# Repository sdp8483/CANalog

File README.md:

# CANalog

CAN to analog converter.

## TODO
### PCB
- [x] Add resistor to stm32 reset line so that stm32 programmer can reset uC when esp8266 is pulling pin high
- [x] Increase clearance between terminals and mounting holes by about 1mm
- [x] Increase spacing between aout terminal and CAN terminal, possibly center CAN terminal.
- [ ] add 16bit DAC
### WiFi Interface Firmware
- [ ] fix webpage layout for mobile devices
- [ ] aout control for analog calibration
- [ ] setup over the air update for esp8266 firmware
### CAN Interface Firmware
- [ ] LED persistance for CAN activity
- [ ] setup bootloader over spi for wifi update of firmware
- [ ] setup CAN filtering
- [ ] test std ID CAN messages
- [ ] test timing
- [ ] write code to detect versioning pins

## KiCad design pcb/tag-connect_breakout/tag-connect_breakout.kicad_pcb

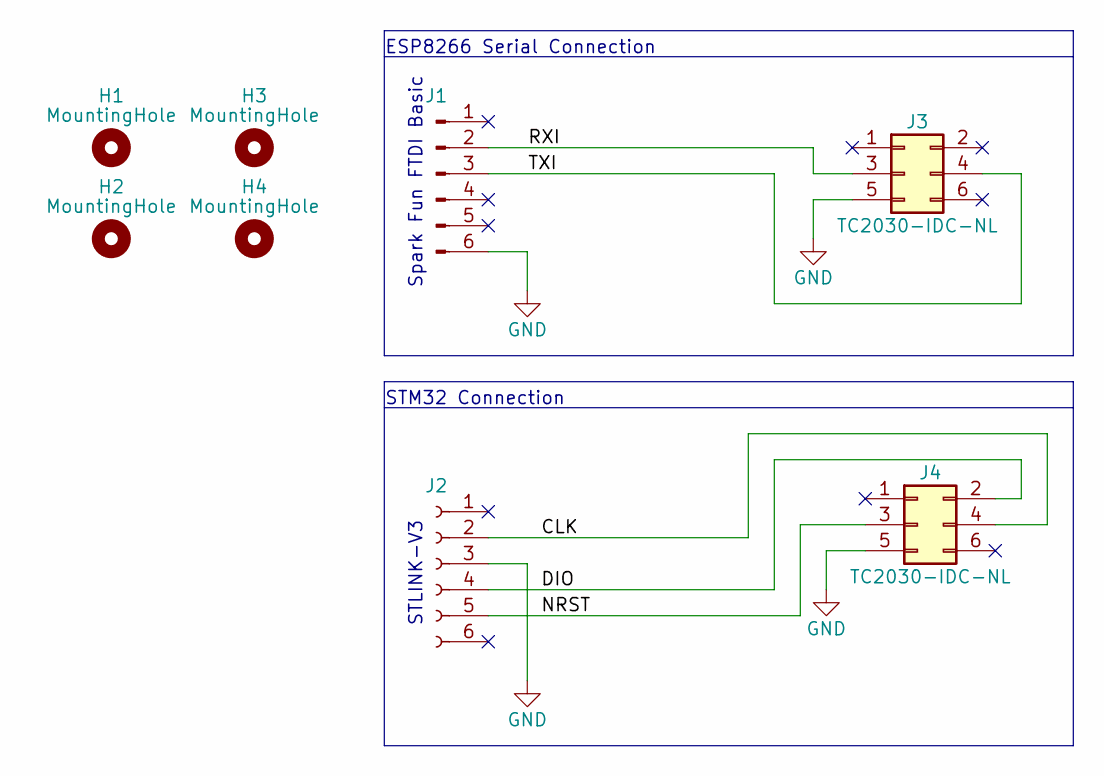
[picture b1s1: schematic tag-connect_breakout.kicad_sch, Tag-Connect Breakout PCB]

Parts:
H1, H2, H3, H4: MountingHole; MountingHole_3.2mm_M3
J1: Conn_01x06_Male; PinHeader_1x06_P2.54mm_Vertical
J2: Conn_01x06_Female; PinSocket_1x06_P2.54mm_Vertical
J3, J4: TC2030-IDC-NL; PinHeader_2x03_P2.54mm_Vertical

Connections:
/CLK: J2.2, J4.4
/DIO: J2.4, J4.2
/NRST: J2.5, J4.3
/RXI: J1.2, J3.3
/TXI: J1.3, J3.4
GND: J1.6, J2.3, J3.5, J4.5

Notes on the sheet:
Spark Fun FTDI Basic
STM32 Connection
ESP8266 Serial Connection
STLINK-V3

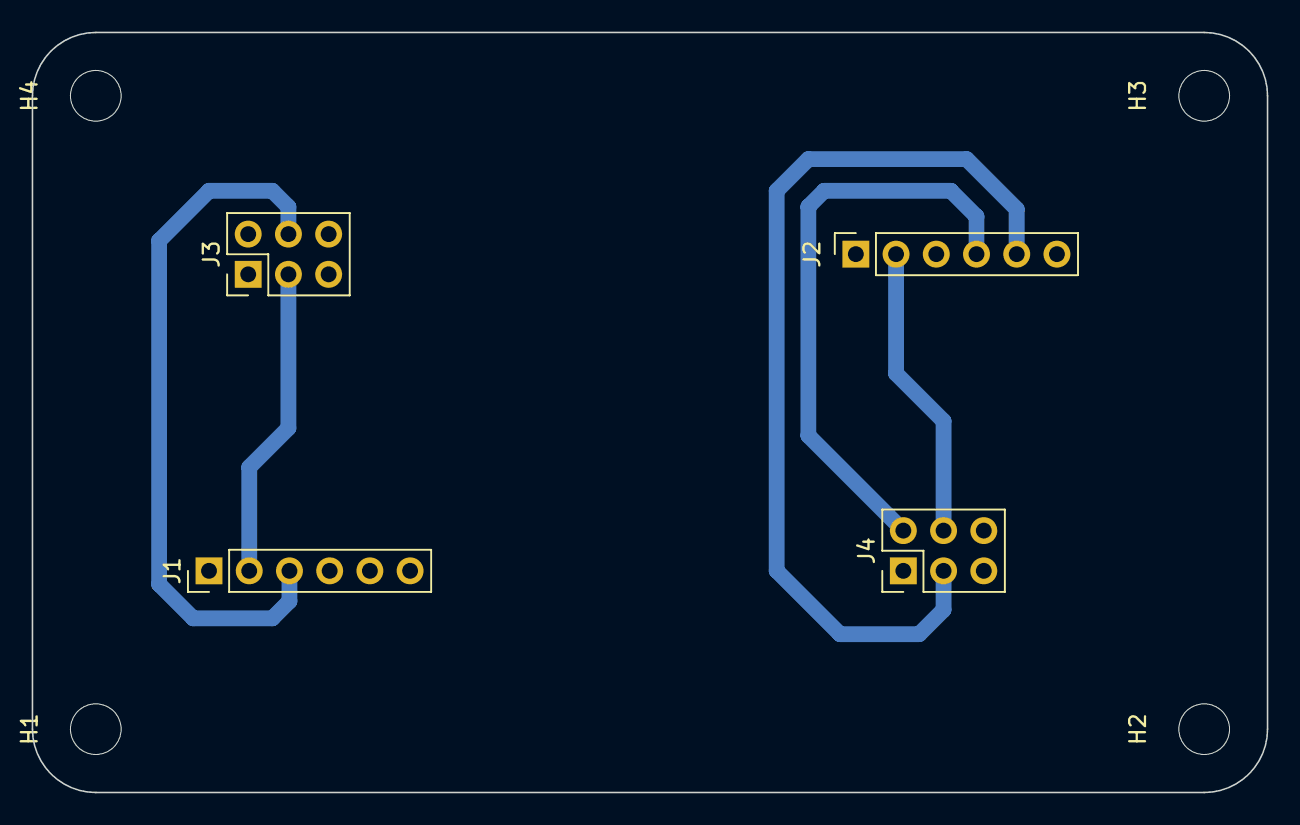
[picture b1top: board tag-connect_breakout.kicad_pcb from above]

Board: 2 copper layers, 78.0 x 48.0 mm, 8 parts (0 on the bottom side), 6 nets.

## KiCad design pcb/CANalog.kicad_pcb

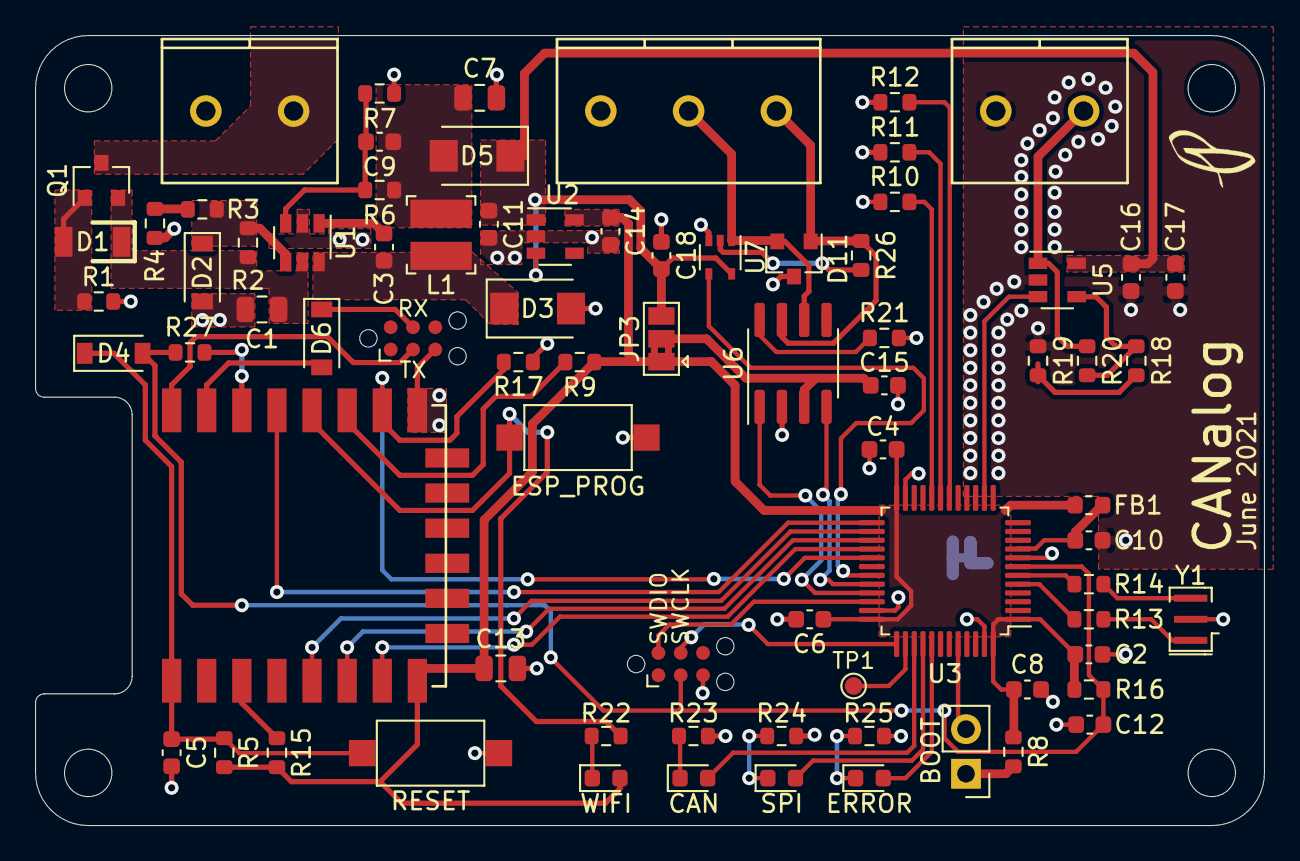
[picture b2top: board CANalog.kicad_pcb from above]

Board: 2 copper layers, 70.0 x 45.0 mm, 82 parts (1 on the bottom side), 59 nets.

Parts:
C1: 4.7uF; C_0805_2012Metric
C2, C11, C14, C17: 1uF; C_0603_1608Metric
C3, C4, C5, C6, C8, C10, C12, C15, C16, C18: 100nF; C_0603_1608Metric
C7, C13: 10uF; C_0805_2012Metric
C9: 33pF; C_0603_1608Metric
D1: BZV55-C15; Nexperia_BZV55_SOD80C
D2: 4.7V; D_SOD-123
D3, D5: SS14F; SMAF
D4, D6: 1N4148W; D_SOD-123
D7: GRN; LED_0603_1608Metric
D8: ORG; LED_0603_1608Metric
D9: RED; LED_0603_1608Metric
D10: BLU; LED_0603_1608Metric
D11: PESD1CAN; SOT-23
FB1: FBS; L_0603_1608Metric
H1, H2, H3, H4: MountingHole; MountingHole_2.7mm_M2.5
J1: PWR; WJ127-5.0-2P
J4: STM_PROG; Tag-Connect_TC2030-IDC-NL_2x03_P1.27mm_Vertical
J5: ESP_PROG; Tag-Connect_TC2030-IDC-NL_2x03_P1.27mm_Vertical
J6: AOUT; WJ127-5.0-2P
J7: CAN; WJ127-5.0-3P
JP2: BOOT0; PinHeader_1x02_P2.54mm_Vertical
JP3: PSELECT; SolderJumper-3_P1.3mm_Bridged2Bar12_Pad1.0x1.5mm
L1: 2.2uH; L_3.5mmx3.0mm_SMD
NT1: Net-Tie_2; NetTie-2_SMD_Pad0.5mm
Q1: DMP3099L-7; SOT-23
R1, R5, R9, R15, R16, R17: 10k; R_0603_1608Metric
R2, R18: 120k; R_0603_1608Metric
R3: 20k; R_0603_1608Metric
R4, R19: 12k; R_0603_1608Metric
R6: 124k; R_0603_1608Metric
R7: 20.5k; R_0603_1608Metric
R8, R10, R11, R12, R22, R23, R24, R25, R27: 1k; R_0603_1608Metric
R13, R14: R; R_0603_1608Metric
R20: 68k; R_0603_1608Metric
R21: 0; R_0603_1608Metric
R26: 120; R_0603_1608Metric
SW1: RESET; SW_SPST_CK_RS282G05A3
SW2: ESP_PROG; SW_SPST_CK_RS282G05A3
TP1: PA15; TestPoint_Pad_D1.0mm
U1: BL9342; SOT-23-6
U2: MIC5504-3.3YM5; SOT-23-5
U3: STM32F302C8T6; LQFP-48_7x7mm_P0.5mm
U4: ESP-12F; ESP-12E_SMD
U5: OPA330xxDBV; SOT-23-5
U6: SN65HVD230; SOIC-8_3.9x4.9mm_P1.27mm
U7: 74AHC1G66; SOT-353_SC-70-5
Y1: 16MHz; Resonator_SMD_muRata_CSTxExxV-3Pin_3.0x1.1mm

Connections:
+3V3: C2.1, C4.1, C6.1, C8.1, C13.1, C14.1, D10.2, FB1.1, JP3.1, R5.1, R8.1, R9.1, R15.1, R16.1, U2.5, U3.1, U3.24, U3.36, U3.48, U4.8
+5V: C11.1, C16.1, C17.1, C18.2, D5.1, JP3.3, U2.1, U2.3, U5.5, U7.5
/5V5: C7.1, C9.1, D5.2, L1.2, R6.1
/BOOT0: JP2.2, U3.44
/CANH: D11.1, J7.1, R26.1, U6.7
/CANL: D11.2, J7.2, U6.6, U7.1
/GPIO15: R27.2, U4.14
/OA_PWR: C15.2, JP3.2, U6.3
/RXD: D6.2, U4.15
/SWCLK: J4.4, U3.37
/SWDIO: J4.2, U3.34
/TXD: J5.3, U4.16
/Vin: C1.1, D1.1, Q1.2, R2.2, U1.5
/XIN: R13.1, U3.5
/XOUT: R14.1, U3.6
CAN_LED: D7.2, U3.39
CAN_RX: U3.32, U6.4
CAN_TERM: U3.31, U7.4
CAN_TX: U3.33, U6.1
CH_PD: R15.2, U4.3
DAC: U3.14, U5.3
ERROR_LED: D9.2, U3.41
ESP_RESET: C5.1, D4.1, R5.2, SW1.2, U4.1
GND: C1.2, C2.2, C4.2, C5.2, C6.2, C7.2, C8.2, C11.2, C12.1, C13.2, C14.2, C15.1, C18.1, D2.2, D3.2, D11.3, J1.2, J4.5, J5.5, J7.3, NT1.1, R1.2, R4.1, R7.1, R10.1, R11.1, R12.1, R17.2, R21.2, R23.1, R24.1, R25.1, SW1.1, SW2.1, U1.2, U2.2, U3.23, U3.35, U3.47, U4.9, U6.2, U7.3, Y1.2
GNDA: C10.2, C16.2, C17.2, J6.2, NT1.2, R19.2, U3.8, U5.2
GPIO0: R22.2, SW2.2, U4.12
GPIO2: R9.2, U4.11
MISO: U3.27, U4.6
MOSI: U3.28, U4.7
unnamed: C3.1, D3.1, L1.1, U1.6
unnamed: C3.2, U1.1
unnamed: C9.2, R6.2, R7.2, U1.3
unnamed: D1.2, Q1.1, R1.1
unnamed: D2.1, R2.1, R3.2, U1.4
unnamed: D6.1, J5.4
unnamed: D7.1, R23.2
unnamed: D8.1, R24.2
unnamed: D9.1, R25.2
unnamed: D10.1, R22.1
unnamed: J1.1, Q1.3
unnamed: J6.1, R20.1, U5.1
unnamed: JP2.1, R8.2
unnamed: R3.1, R4.2
unnamed: R13.2, Y1.1
unnamed: R14.2, Y1.3
unnamed: R18.1, R20.2, U5.4
unnamed: R18.2, R19.1
unnamed: R21.1, U6.8
unnamed: R26.2, U7.2
unnamed: TP1.1, U3.38
SCLK: U3.26, U4.5
SPI_LED: D8.2, U3.40
STM_CS: R17.1, U3.29, U4.10
STM_RDY: U3.25, U4.13
STM_RESET: C12.2, D4.2, J4.3, R16.2, R27.1, U3.7
VDDA: C10.1, FB1.2, U3.9
V_B0: R12.2, U3.18
V_B1: R11.2, U3.19
V_B2: R10.2, U3.20

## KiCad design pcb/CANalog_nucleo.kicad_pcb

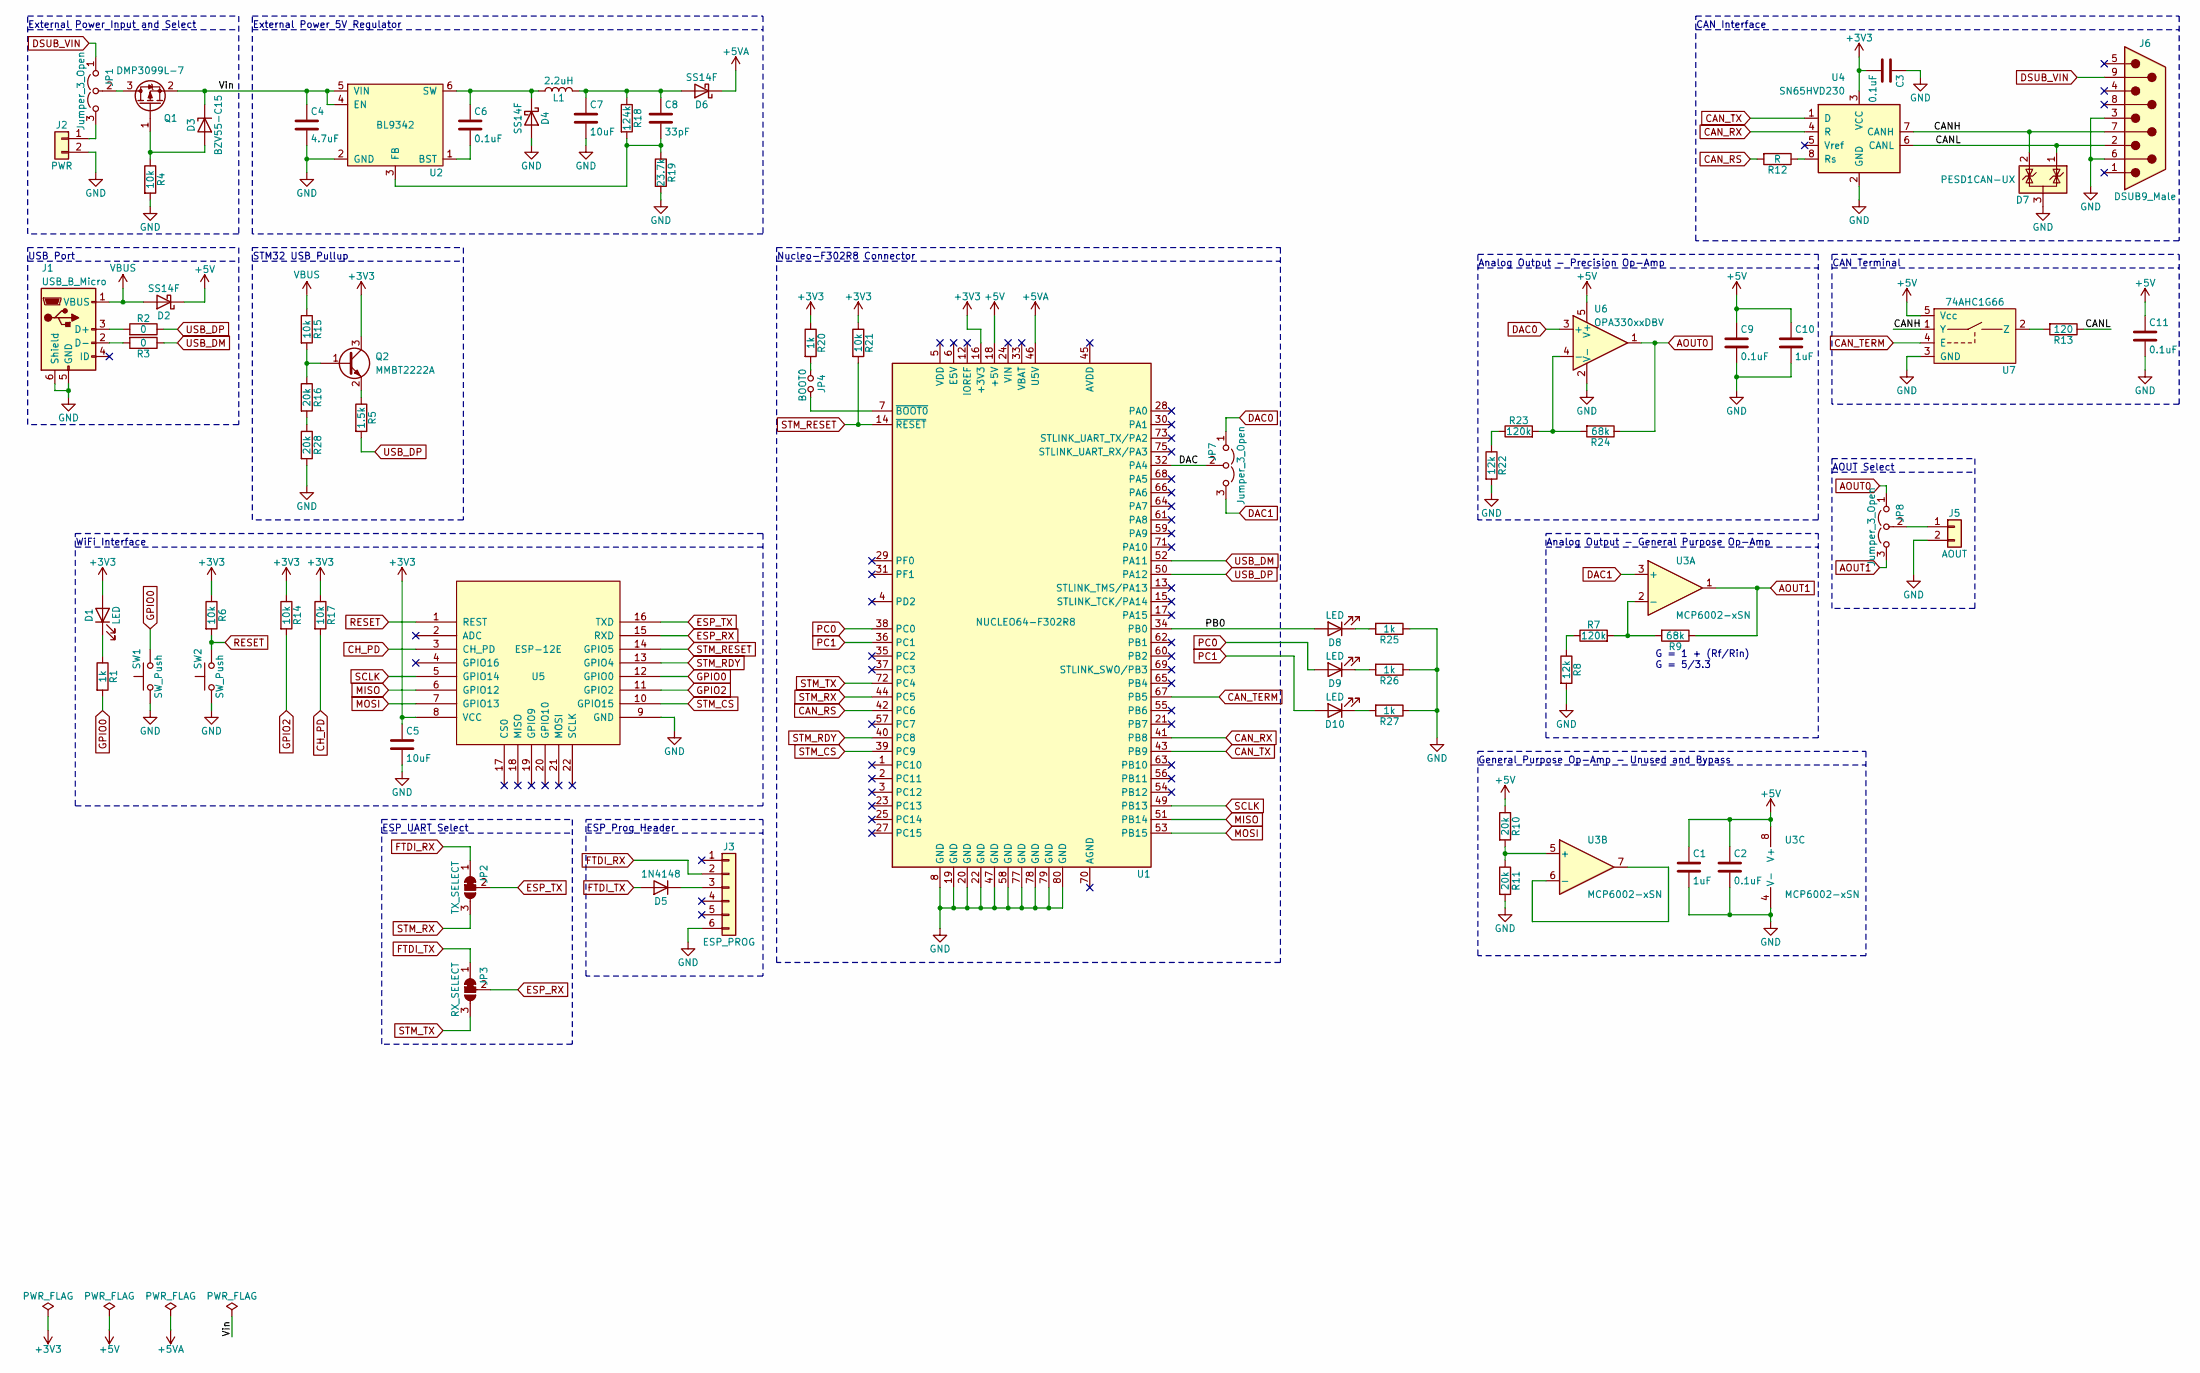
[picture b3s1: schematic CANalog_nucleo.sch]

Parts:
C1, C10: 1uF; C_0805_2012Metric
C2, C3, C6, C9, C11: 0.1uF; C_0805_2012Metric
C4: 4.7uF; C_0805_2012Metric
C5, C7: 10uF; C_0805_2012Metric
C8: 33pF; C_0603_1608Metric
D1, D8, D9, D10: LED; LED_0603_1608Metric
D2, D4, D6: SS14F; SMAF
D3: BZV55-C15; Nexperia_BZV55_SOD80C
D5: 1N4148; D_DO-35_SOD27_P7.62mm_Horizontal
D7: PESD1CAN-UX; SOT-323_SC-70
J1: USB_B_Micro; USB_Micro-B_Amphenol_10103594-0001LF_Horizontal
J2: PWR; WJ127-5.0-2P
J3: ESP_PROG; PinHeader_1x06_P2.54mm_Vertical
J5: AOUT; WJ127-5.0-2P
J6: DSUB9_Male; DSUB-9_Male_Horizontal_P2.77x2.84mm_EdgePinOffset7.70mm_Hou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
JP1, JP7, JP8: Jumper_3_Open; PinHeader_1x03_P2.54mm_Vertical
JP2: TX_SELECT; SolderJumper-3_P1.3mm_Bridged12_RoundedPad1.0x1.5mm
JP3: RX_SELECT; SolderJumper-3_P1.3mm_Bridged12_RoundedPad1.0x1.5mm
JP4: BOOT0; PinHeader_1x02_P2.54mm_Vertical
L1: 2.2uH; L_3.5mmx3.0mm_SMD
Q1: DMP3099L-7; SOT-23
Q2: MMBT2222A; SOT-23
R1, R20, R25, R26, R27: 1k; R_0805_2012Metric
R2, R3: 0; R_0805_2012Metric
R4, R6, R14, R15, R17, R21: 10k; R_0805_2012Metric
R5: 1.5k; R_0805_2012Metric
R7, R23: 120k; R_0805_2012Metric
R8, R22: 12k; R_0805_2012Metric
R9, R24: 68k; R_0805_2012Metric
R10, R11, R16, R28: 20k; R_0805_2012Metric
R12: R; R_0805_2012Metric
R13: 120; R_0805_2012Metric
R18: 124k; R_0805_2012Metric
R19: 23.7k; R_0805_2012Metric
SW1, SW2: SW_Push; SW_PUSH_6mm
U1: NUCLEO64-F302R8; nucleo-f302r8
U2: BL9342; SOT-23-6
U3: MCP6002-xSN; SOIC-8_3.9x4.9mm_P1.27mm
U4: SN65HVD230; SOIC-8_3.9x4.9mm_P1.27mm
U5: ESP-12E; ESP-12E_SMD
U6: OPA330xxDBV; SOT-23-5
U7: 74AHC1G66; SOT-353_SC-70-5

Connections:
+3V3: C3.2, C5.1, D1.2 (A), Q2.3 (C), R6.1, R14.1, R17.1, R20.1, R21.1, U1.16 (+3V3), U4.3 (VCC), U5.8 (VCC)
+5V: C1.1, C2.1, C9.1, C10.1, C11.1, D2.1 (K), R10.1, U1.18 (+5V), U3.8 (V+), U6.5 (V+), U7.5 (Vcc)
+5VA: D6.1 (K), U1.46 (U5V)
/CANH: D7.2 (K), J6.7, U4.7 (CANH), U7.1 (Y)
/CANL: D7.1 (K), J6.2, R13.1, U4.6 (CANL)
/DAC: JP7.2 (C), U1.32 (PA4)
/PB0: D8.2 (A), U1.34 (PB0)
/Vin: C4.1, D3.1 (K), Q1.2 (S), U2.4 (EN), U2.5 (VIN)
AOUT0: JP8.1 (A), R24.1, U6.1
AOUT1: JP8.3 (B), R9.1, U3.1
CAN_RS: R12.2, U1.42 (PC6)
CAN_RX: U1.41 (PB8), U4.4 (R)
CAN_TERM: U1.67 (PB5), U7.4 (E)
CAN_TX: U1.43 (PB9), U4.1 (D)
CH_PD: R17.2, U5.3 (CH_PD)
DAC0: JP7.1 (A), U6.3 (+)
DAC1: JP7.3 (B), U3.3 (+)
DSUB_VIN: J6.9, JP1.1 (A)
ESP_RX: JP3.2 (C), U5.15 (RXD)
ESP_TX: JP2.2 (C), U5.16 (TXD)
FTDI_RX: J3.2, JP2.1 (A)
FTDI_TX: D5.2 (A), JP3.1 (A)
GND: C1.2, C2.2, C3.1, C4.2, C5.2, C7.2, C9.2, C10.2, C11.2, D4.2 (A), D7.3 (A), J1.5 (GND), J1.6 (Shield), J2.2, J3.6, J5.2, J6.3, J6.6, R4.2, R8.2, R11.2, R19.2, R22.2, R25.1, R26.1, R27.1, R28.2, SW1.1, SW2.1, U1.8 (GND), U1.19 (GND), U1.20 (GND), U1.22 (GND), U1.47 (GND), U1.58 (GND), U1.77 (GND), U1.78 (GND), U1.79 (GND), U1.80 (GND), U2.2 (GND), U3.4 (V-), U4.2 (GND), U5.9 (GND), U6.2 (V-), U7.3 (GND)
GPIO0: R1.2, SW1.2, U5.12 (GPIO0)
GPIO2: R14.2, U5.11 (GPIO2)
MISO: U1.51 (PB14), U5.6 (GPIO12)
MOSI: U1.53 (PB15), U5.7 (GPIO13)
unnamed: C6.1, D4.1 (K), L1.1, U2.6 (SW)
unnamed: C6.2, U2.1 (BST)
unnamed: C7.1, C8.1, D6.2 (A), L1.2, R18.1
unnamed: C8.2, R18.2, R19.1, U2.3 (FB)
unnamed: D1.1 (K), R1.1
unnamed: D3.2 (A), Q1.1 (G), R4.1
unnamed: D5.1 (K), J3.3
unnamed: D8.1 (K), R25.2
unnamed: D9.1 (K), R26.2
unnamed: D10.1 (K), R27.2
unnamed: J1.2 (D-), R3.2
unnamed: J1.3 (D+), R2.2
unnamed: J2.1, JP1.3 (B)
unnamed: J5.1, JP8.2 (C)
unnamed: JP1.2 (C), Q1.3 (D)
unnamed: JP4.1, R20.2
unnamed: JP4.2, U1.7 (~BOOT0)
unnamed: Q2.1 (B), R15.2, R16.1
unnamed: Q2.2 (E), R5.1
unnamed: R7.1, R8.1
unnamed: R7.2, R9.2, U3.2 (-)
unnamed: R10.2, R11.1, U3.5 (+)
unnamed: R12.1, U4.8 (Rs)
unnamed: R13.2, U7.2 (Z)
unnamed: R16.2, R28.1
unnamed: R22.1, R23.1
unnamed: R23.2, R24.2, U6.4 (-)
unnamed: U3.6 (-), U3.7
PC0: D9.2 (A), U1.38 (PC0)
PC1: D10.2 (A), U1.36 (PC1)
RESET: R6.2, SW2.2, U5.1 (REST)
SCLK: U1.49 (PB13), U5.5 (GPIO14)
STM_CS: U1.39 (PC9), U5.10 (GPIO15)
STM_RDY: U1.40 (PC8), U5.13 (GPIO4)
STM_RESET: R21.2, U1.14 (~RESET), U5.14 (GPIO5)
STM_RX: JP2.3 (B), U1.44 (PC5)
STM_TX: JP3.3 (B), U1.72 (PC4)
USB_DM: R3.1, U1.52 (PA11)
USB_DP: R2.1, R5.2, U1.50 (PA12)
VBUS: D2.2 (A), J1.1 (VBUS), R15.1

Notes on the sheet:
G = 1 + (Rf/Rin) G = 5/3.3
General Purpose Op-Amp - Unused and Bypass
CAN Interface
USB Port
Nucleo-F302R8 Connector
Analog Output - General Purpose Op-Amp
STM32 USB Pullup
External Power 5V Regulator
Analog Output - Precision Op-Amp
CAN Terminal
External Power Input and Select
AOUT Select
ESP UART Select
ESP Prog Header
WiFi Interface

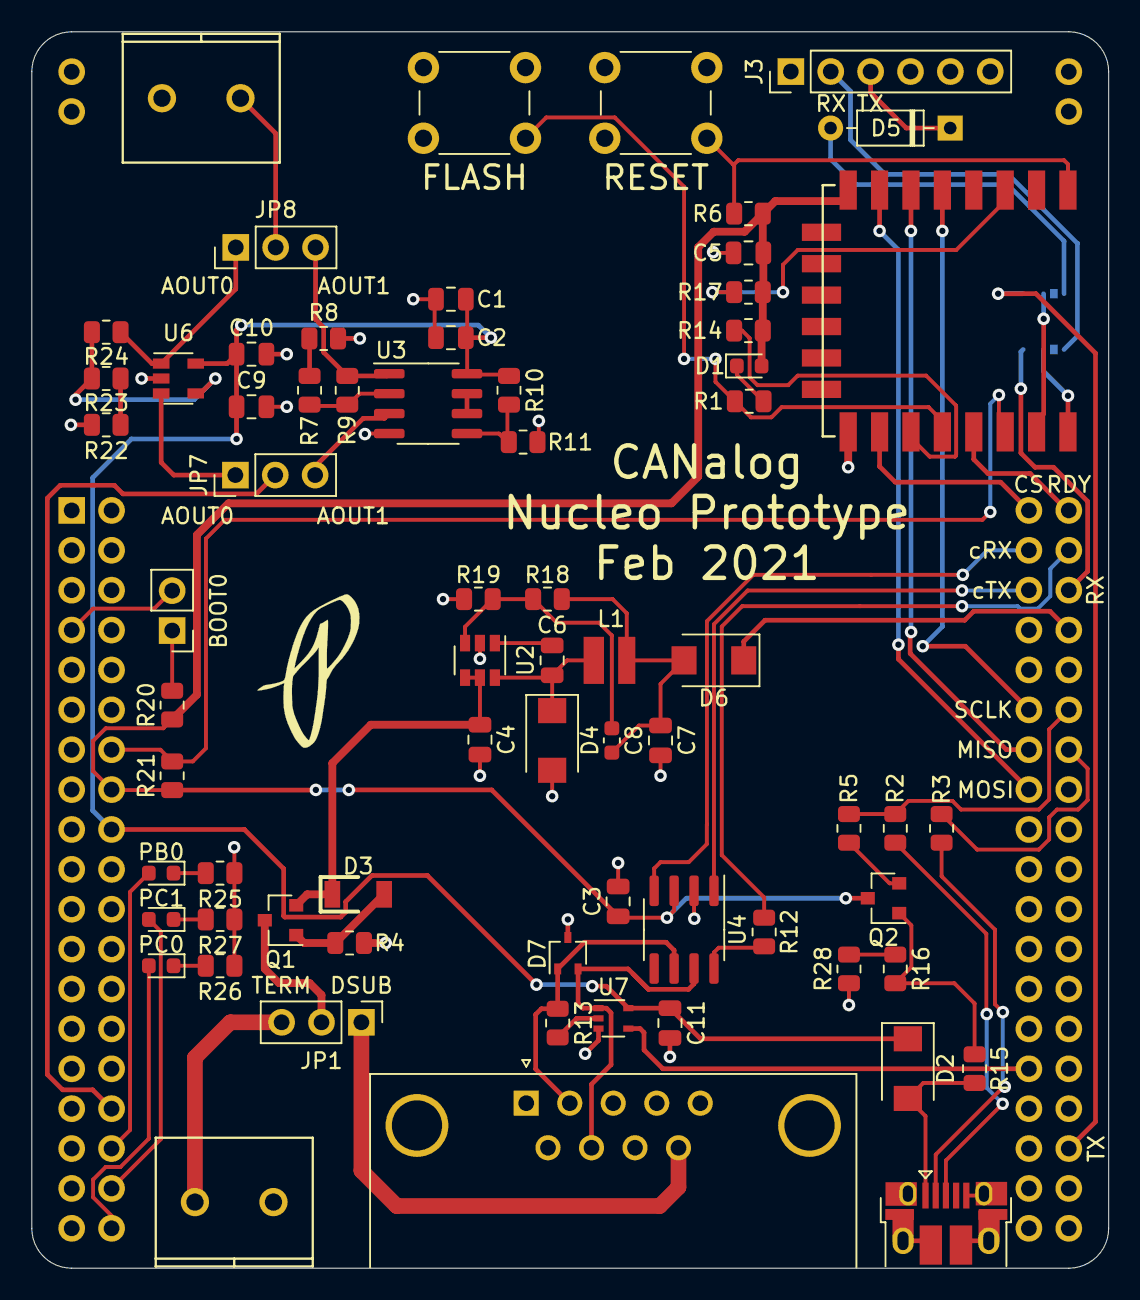
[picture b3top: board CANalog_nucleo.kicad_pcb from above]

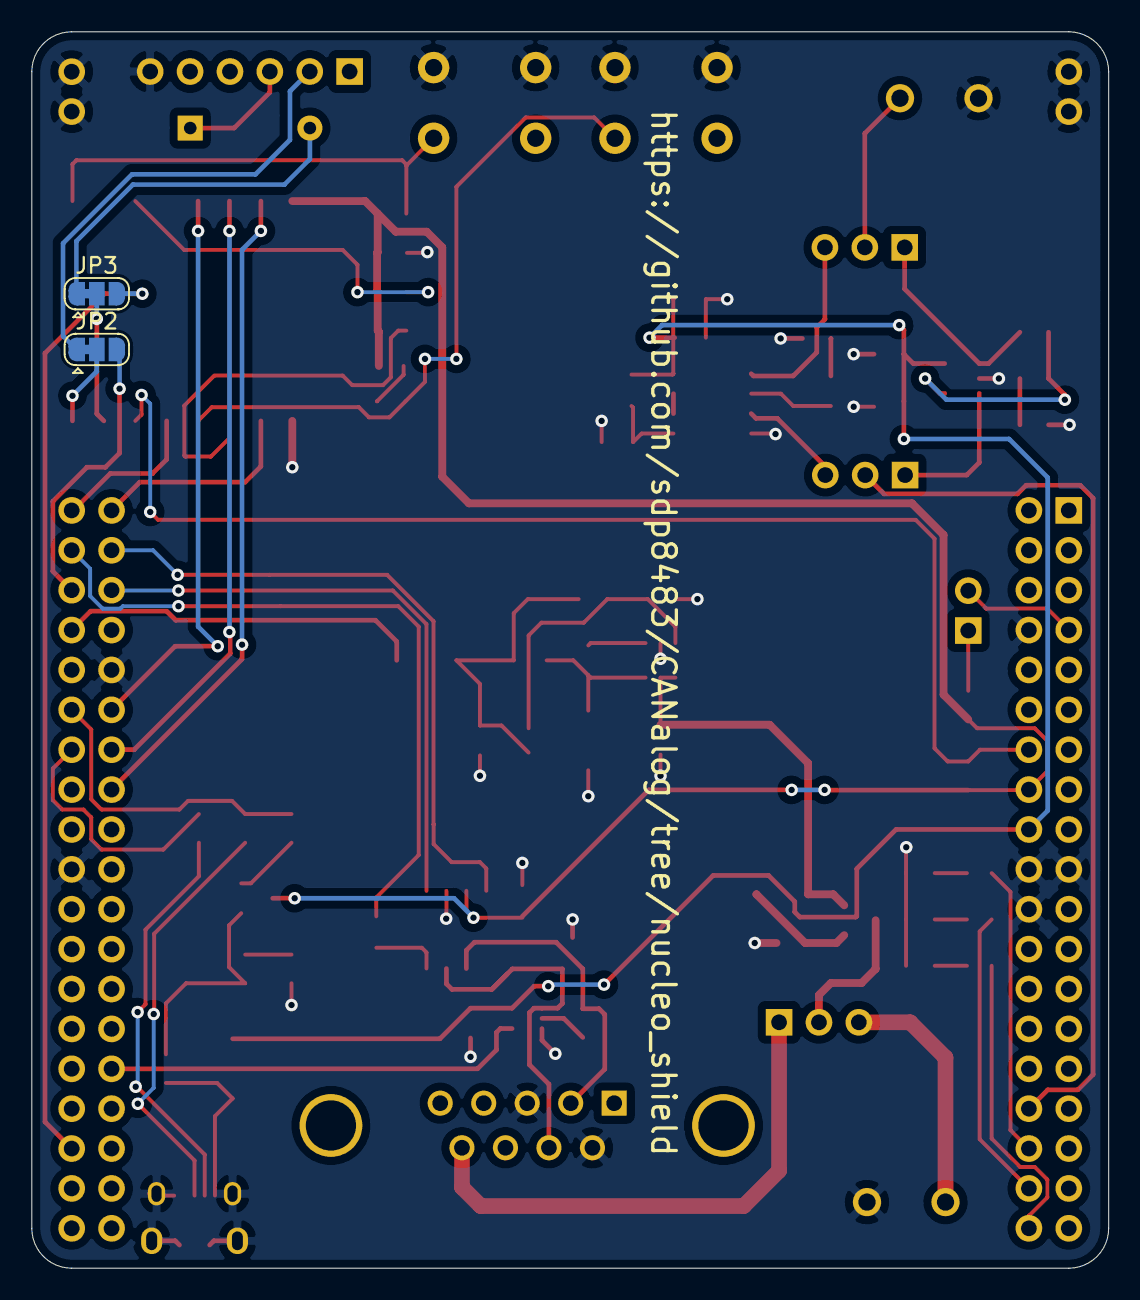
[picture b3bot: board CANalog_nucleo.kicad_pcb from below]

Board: 2 copper layers, 68.6 x 78.7 mm, 72 parts (2 on the bottom side), 67 nets.

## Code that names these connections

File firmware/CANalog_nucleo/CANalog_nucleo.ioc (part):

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Mcu.UserName=STM32F302R8Tx
PC9.GPIO_Label=CS
RCC.SYSCLKSourceVirtual=RCC_SYSCLKSOURCE_PLLCLK
PC0.GPIOParameters=GPIO_Label
PC8.Signal=GPIO_Output
PC6.Signal=GPIO_Output
PC6.GPIO_Label=CAN_RS
PC0.GPIO_Label=LED1
PB0.GPIO_Label=LED0
RCC.HSEPLLFreq_Value=8000000
PC0.Signal=GPIO_Output
PB13.Signal=SPI2_SCK
PB15.Signal=SPI2_MOSI
PB5.GPIOParameters=GPIO_Label
PC8.PinState=GPIO_PIN_SET
PC8.GPIO_Label=RDY
PA13.Signal=SYS_JTMS-SWDIO
PC1.GPIOParameters=GPIO_Label
PB9.Mode=CAN_Activate
PB14.Signal=SPI2_MISO
RCC.HSE_VALUE=8000000
board=custom
PB15.Mode=Full_Duplex_Slave
PB0.GPIOParameters=GPIO_Label
PA14.Mode=Serial_Wire
PB14.Mode=Full_Duplex_Slave
PC1.GPIO_Label=LED2
PA13.Mode=Serial_Wire
PC9.GPIOParameters=GPIO_Label
Mcu.Name=STM32F302R(6-8)Tx
PC8.GPIOParameters=GPIO_Label,GPIO_Speed,PinState
PA4.Signal=COMP_DAC1_group
RCC.SYSCLKFreq_VALUE=64000000
Mcu.Package=LQFP64
PB5.Signal=GPIO_Output
PB9.Signal=CAN_TX
PA14.Signal=SYS_JTCK-SWCLK
PC6.GPIOParameters=GPIO_Label
PC8.GPIO_Speed=GPIO_SPEED_FREQ_HIGH
PB5.GPIO_Label=CAN_TERM
PB8.Mode=CAN_Activate
PB8.Signal=CAN_RX
PB13.Mode=Full_Duplex_Slave
PC9.Signal=GPIO_Input
PB0.Signal=GPIO_Output
PC1.Signal=GPIO_Output

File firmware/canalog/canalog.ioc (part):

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Mcu.UserName=STM32F302C8Tx
RCC.SYSCLKSourceVirtual=RCC_SYSCLKSOURCE_PLLCLK
PA11.Mode=CAN_Activate
PB0.GPIO_Label=V_B0
RCC.HSEPLLFreq_Value=16000000
PB13.Signal=SPI2_SCK
PB15.Signal=SPI2_MOSI
PB5.GPIOParameters=GPIO_Label
PB4.GPIOParameters=GPIO_Label
PA12.Signal=CAN_TX
PB1.GPIO_PuPd=GPIO_PULLUP
PA8.GPIOParameters=GPIO_Label
RCC.HSE_VALUE=16000000
PB2.Signal=GPIO_Input
PB12.GPIO_Label=SPI2_RDY
PB0.GPIOParameters=GPIO_PuPd,GPIO_Label
PA14.Mode=Serial_Wire
PB14.Mode=Full_Duplex_Slave
PB1.GPIO_Label=V_B1
PA10.GPIO_Label=CAN_TERM
PB3.GPIOParameters=GPIO_Label
PA8.Signal=GPIO_Input
PB2.GPIO_PuPd=GPIO_PULLUP
Mcu.Package=LQFP48
PB1.Signal=GPIO_Input
PA10.Signal=GPIO_Output
PA15.Signal=GPIO_Output
PB5.GPIO_Label=ERROR_LED
PB13.Mode=Full_Duplex_Slave
PF1-OSC_OUT.Mode=HSE-External-Oscillator
PF1-OSC_OUT.Signal=RCC_OSC_OUT
PB4.Signal=GPIO_Output
PB3.GPIO_Label=CAN_LED
PA13.Signal=SYS_JTMS-SWDIO
PA8.GPIO_Label=SPI2_CS
PB2.GPIOParameters=GPIO_PuPd,GPIO_Label
PF0-OSC_IN.Mode=HSE-External-Oscillator
PB14.Signal=SPI2_MISO
board=custom
PB15.Mode=Full_Duplex_Slave
PB4.GPIO_Label=SPI_LED
PA10.GPIOParameters=GPIO_Label
PA13.Mode=Serial_Wire
Mcu.Name=STM32F302C(6-8)Tx
PB3.Signal=GPIO_Output
PA4.Signal=COMP_DAC1_group
RCC.SYSCLKFreq_VALUE=48000000
PB5.Signal=GPIO_Output
PA12.Mode=CAN_Activate
PA11.Signal=CAN_RX
PA14.Signal=SYS_JTCK-SWCLK
PB2.GPIO_Label=V_B2
PF0-OSC_IN.Signal=RCC_OSC_IN
PB0.Signal=GPIO_Input
PB12.GPIOParameters=GPIO_Label
PB12.Signal=GPIO_Output
PB0.GPIO_PuPd=GPIO_PULLUP
PB1.GPIOParameters=GPIO_PuPd,GPIO_Label

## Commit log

2021-01-10 init commit
2021-01-11 start shematic
2021-01-23 start schema
2021-01-24 schematic done
2021-01-24 add 3d models
2021-01-24 quickand dirty prototype
2021-01-24 generate gerbers
2021-01-24 output pdf
2021-01-24 generate ibom
2021-01-24 generate bare bones firmware, HAL code setup
2021-01-25 esp01 interface start code, getting there
2021-01-26 use correct device name
2021-01-26 cleanup
2021-01-27 getting there
2021-01-28 more inputs
2021-01-28 play with UART command parsing, needs help
2021-01-31 uart command parser working
2021-01-31 send all data as DEC
2021-02-01 cmd parsing at startup
2021-02-01 receive CAN id as DEC
2021-02-01 stuff and things
2021-02-02 uart issues
2021-02-02 working uart communication but esp double sends get commands
2021-02-03 esp8266 saves data, only SN is passed between them
2021-02-03 no need for state machine
2021-02-03 dac play
2021-02-04 fixed can to analog
2021-02-04 new config layout
2021-02-06 signal in frame calulations
2021-02-07 Update signal_in_frame
2021-02-07 add more features
2021-02-07 baud switching, not tested much
2021-02-07 add new parameters
2021-02-07 add new commands
2021-02-07 formating and send values on startup
2021-02-07 number format fix
2021-02-07 specify upload port
2021-02-07 more can stop
2021-02-07 big endian bit shift fix
2021-02-07 value send timout and retry error detection
2021-02-07 error screen format
2021-02-09 add DNS
2021-02-09 parameter checks
2021-02-11 increase bit max value
2021-02-12 add frame page
2021-02-13 place html test files in new dir
2021-02-14 webpages in header files
2021-02-15 add logic probe data and setup
2021-02-15 implement SPI interface with STM32
2021-02-16 add spi
2021-02-18 interupt main loop flag
2021-02-18 update board
2021-02-19 redo stm32 project file
2021-02-19 spi polling with ready pin
2021-02-19 add spi rdy pin
2021-02-19 Create spi_with_rdy
2021-02-20 recalc sn on signal_update
2021-02-20 spi error handling
2021-02-20 add rdy_pin timeout
2021-02-20 stm32 reset pin
2021-02-21 update schematic
2021-02-22 start new pcb layout
2021-02-24 layout getting there
2021-03-02 layout done
2021-03-04 add all possible can bauds rates
2021-03-04 cleanup comments
2021-03-04 increase fcpu to 160MHz
2021-03-04 start local server for webpage testing
2021-03-05 rename to filename used by esp
2021-03-05 change name to match esp server page name
2021-03-05 css seperate file
2021-03-07 upgrade to Async webserver to support future use of websockets
2021-03-08 update ibom
2021-03-09 change RDY and CS pins
2021-03-10 add 10k pulldown on GPIO15 of esp
2021-03-10 add aditional gpio
2021-03-10 blink LEDs
2021-03-14 changed root.html to index.html
2021-03-14 added savedOutput class for save.html
2021-03-14 updated webpages
2021-03-14 enable esp reading stm fw/hw version strings
2021-03-14 cleanup version info section
2021-03-15 add about page
2021-03-17 seperate js files for each page
2021-03-20 remove signal page, combined with frame page
2021-03-20 auto generated headers from webpage files
2021-03-20 implement frame view
2021-03-20 remove analog and frame display webpage
2021-03-20 change about page style
2021-03-22 terminator control
2021-03-22 change command verb to reflect stm32 spi action
2021-03-22 change spi command to reflect data handled
2021-03-23 remove old dir
2021-03-23 rename
2021-03-24 disable favicon request, rearange meta tags
2021-03-24 add simple websocket test page, more to come
2021-03-24 pull spi cs pin high on timeout to release stm32
2021-03-25 webplot CAN signal
2021-03-25 webview dac output
2021-03-25 can frame websocket streaming
2021-03-26 update to new circuitry, work in progress
2021-03-26 frame bit view
2021-03-27 request SN spi command
2021-03-27 fix json data stream bug of frame not sending enough characters
    remeber for HEX data to a string for a leading zero use < 16 not 10!
    was stuck on this for hours!!!!
2021-03-27 display can frame HEX on webpage
2021-03-27 fix big endian
2021-03-27 nibble swap function without for loop
2021-03-28 scematic additions
2021-03-28 track csv files
2021-03-28 preliminary csv bom output
    for inventory tracking
2021-03-28 add polyfuse on usb
2021-03-28 clear capacitor footprints
2021-03-29 start updating part details
2021-03-29 adding details
2021-03-30 add more field info
2021-03-30 add footprint
2021-03-30 add 3d models for terminals
2021-03-30 add CAN terminal footprint
2021-03-30 update 3d model location
2021-03-30 add remaining footprints
2021-03-30 erc cleanup
2021-03-30 add custom diode 3d models
2021-03-30 not used
2021-03-30 move into dir
2021-03-30 add components to pcb
2021-03-31 add overvoltage protection to BL9342 enable pin
    this pin cannot exceed 5V!!!! Learned this the hard way but best to learn it now with the nucleo prototype. RIP dev board.
2021-03-31 create missing 3d model
2021-03-31 update silkscreen and courtyard
2021-03-31 usb fuse part number change to instock
2021-03-31 update ferrite with instock partnumber
2021-03-31 replace agnd jumper to gnd with net tie
2021-03-31 remove ferrite bead on analog output
2021-04-01 analog ground for analog circuit section
2021-04-02 start pcb layout
2021-04-03 update navigation bar to new style
2021-04-13 add sn algorithm generation testing
2021-04-13 remove usb
2021-04-18 remove expansion headers
2021-04-19 start power supply layout
2021-04-19 power supply layout
2021-04-21 update programming connectors to tc2030-idc-nl
2021-04-22 custom title block
2021-04-25 remove can_rs connection to stm32
2021-04-25 stm32 pin swaping
2021-04-25 move tp to pa15
2021-04-25 update pcb layout, first draft
2021-04-30 clean up and silkscreen work
2021-05-04 add canalog logo
2021-05-04 cleanup pcb
2021-05-05 final cleanup
2021-05-05 output gerber
2021-05-15 migrate STM32 code to new pn
2021-05-15 set spi data size to 8bit
2021-05-15 update webpage style
2021-05-15 update iBom with DNP fields missing
2021-05-16 implement WiFi connection LED, update version to 1.0
2021-05-16 fix ibom missing R21
2021-05-16 fix sn calculation array index outside of range
2021-05-17 update with TODO
2021-05-19 set can to silent
2021-05-20 update with label
2021-05-22 increase width 1mm
2021-05-22 update labels
2021-05-22 persistent can led
2021-05-23 remove inside of As
2021-05-23 increase font size
2021-06-16 added resistor between STM32 reset land ESP8266 GPIO15
2021-06-16 clearance around terminals
2021-06-16 enable i2c2, todo implement dac in fw
2021-06-16 add 16bit DAC
2021-06-21 add DAC
2021-06-21 gerber output
2022-02-09 comment spelling fix
2022-02-12 auto generate webpage headers with pre-build script
2022-02-12 remove prototype firmware directory
2022-02-12 move web page files into esp interface firmware
2022-02-12 add OTA for esp8266 firmware
2022-02-12 use TaskScheduler lib for web socket.
2022-02-12 add dac control from wifi interface
2022-02-12 spi is receiving data not sending
2022-02-13 manual analog output control for calibration
2022-02-13 update to kicad 6
2022-02-13 move to separate dir
2022-02-13 create tag-connect adapter
2022-02-19 upgrade to stm32cubeide 1.8
2022-02-19 ignore Debug dir
